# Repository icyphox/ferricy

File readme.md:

# ferricy
> A 34-key split keyboard based on the [Sweep](https://github.com/davidphilipbarr/Sweep/).

Ferricy is a slightly modified version of the Ferris Sweep, sporting a
more industrial look with sharper edges. Notable features:

- Ferricy MX based on the Sweep MX Bling.
- Ferricy Choc based on the Sweep Half-Swept.
- Tenting puck support has been removed (I have no use for it).
- Squared-off edges (plates modified accordingly).
- Larger holes in the PCB for M2 standoffs to pass through.
- The stupid Rust crab is gone.

### MX

| Front | Back |
| :---: | :---: |
|  |  |

### Choc

| Front | Back |
| :---: | :---: |
|  |  |

## license & credits

Ferricy retains [Sweep's
license](https://github.com/davidphilipbarr/Sweep/blob/main/LICENSE).
Thanks to David Barr and all of Sweep's contributors.

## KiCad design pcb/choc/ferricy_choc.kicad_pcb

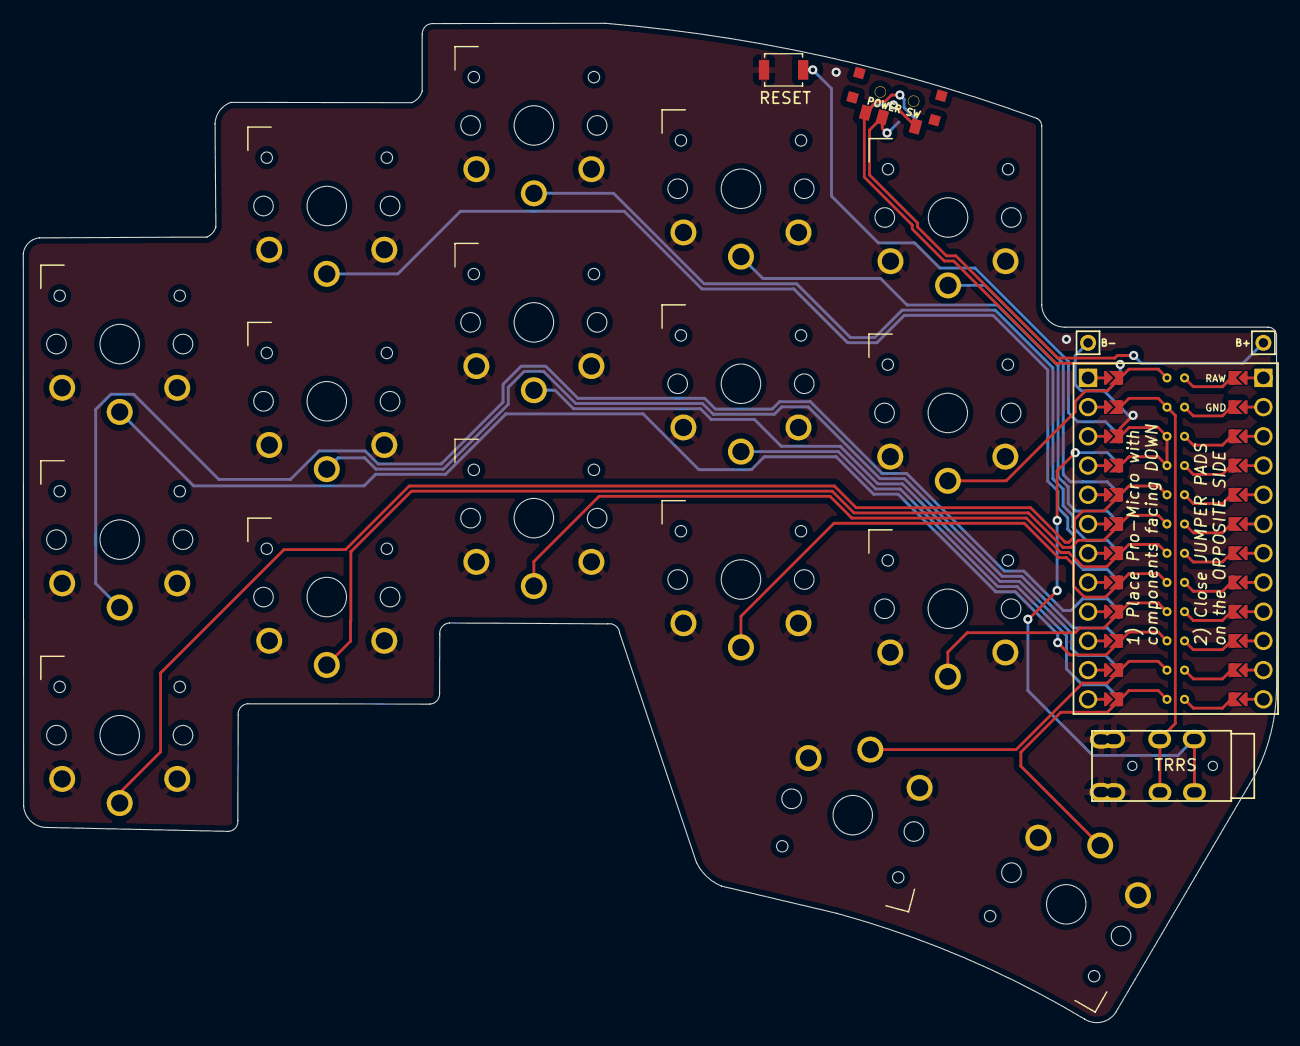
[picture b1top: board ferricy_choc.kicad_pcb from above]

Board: 2 copper layers, 108.9 x 86.9 mm, 23 parts (0 on the bottom side), 23 nets.

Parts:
B+: MountingHole_Pad; 1pin_conn
B-: MountingHole_Pad; 1pin_conn
J2: AudioJack4dpb; TRRS-PJ-DPB2
POWER SW: SW_SPDT; SPDT_C128955
RSW2: SW_Push; Tactile-Switch_SMT
SW1, SW2, SW3, SW4, SW5, SW6, SW7, SW8, SW9, SW10, SW11, SW12, SW13, SW14, SW15, SW16, SW17: SW_Push; SW_PG1350_rev_DPB
U1: ProMicro-kbd; ProMicro_jumpers_facedown

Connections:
BT+_r: B+.1, POWER SW.2
Switch1: SW1.1, U1.10
Switch2: SW2.1, U1.17
Switch3: SW3.1, U1.18
Switch4: SW4.1, U1.19
Switch5: SW5.1, U1.20
Switch6: SW6.1, U1.16
Switch7: SW7.1, U1.15
Switch8: SW8.1, U1.14
Switch9: SW9.1, U1.13
Switch10: SW10.1, U1.1
Switch11: SW11.1, U1.5
Switch12: SW12.1, U1.6
Switch13: SW13.1, U1.7
Switch14: SW14.1, U1.8
Switch15: SW15.1, U1.9
Switch16: SW16.1, U1.11
Switch17: SW17.1, U1.12
Switch18: J2.R1, U1.2
gnd: B-.1, J2.S, J2.T, RSW2.1, RSW2.2, SW1.2, SW2.2, SW3.2, SW4.2, SW5.2, SW6.2, SW7.2, SW8.2, SW9.2, SW10.2, SW11.2, SW12.2, SW13.2, SW14.2, SW15.2, SW16.2, SW17.2, U1.3, U1.4, U1.23
raw: POWER SW.3, U1.24
reset: RSW2.1, RSW2.2, U1.22
vcc: J2.R2, U1.21

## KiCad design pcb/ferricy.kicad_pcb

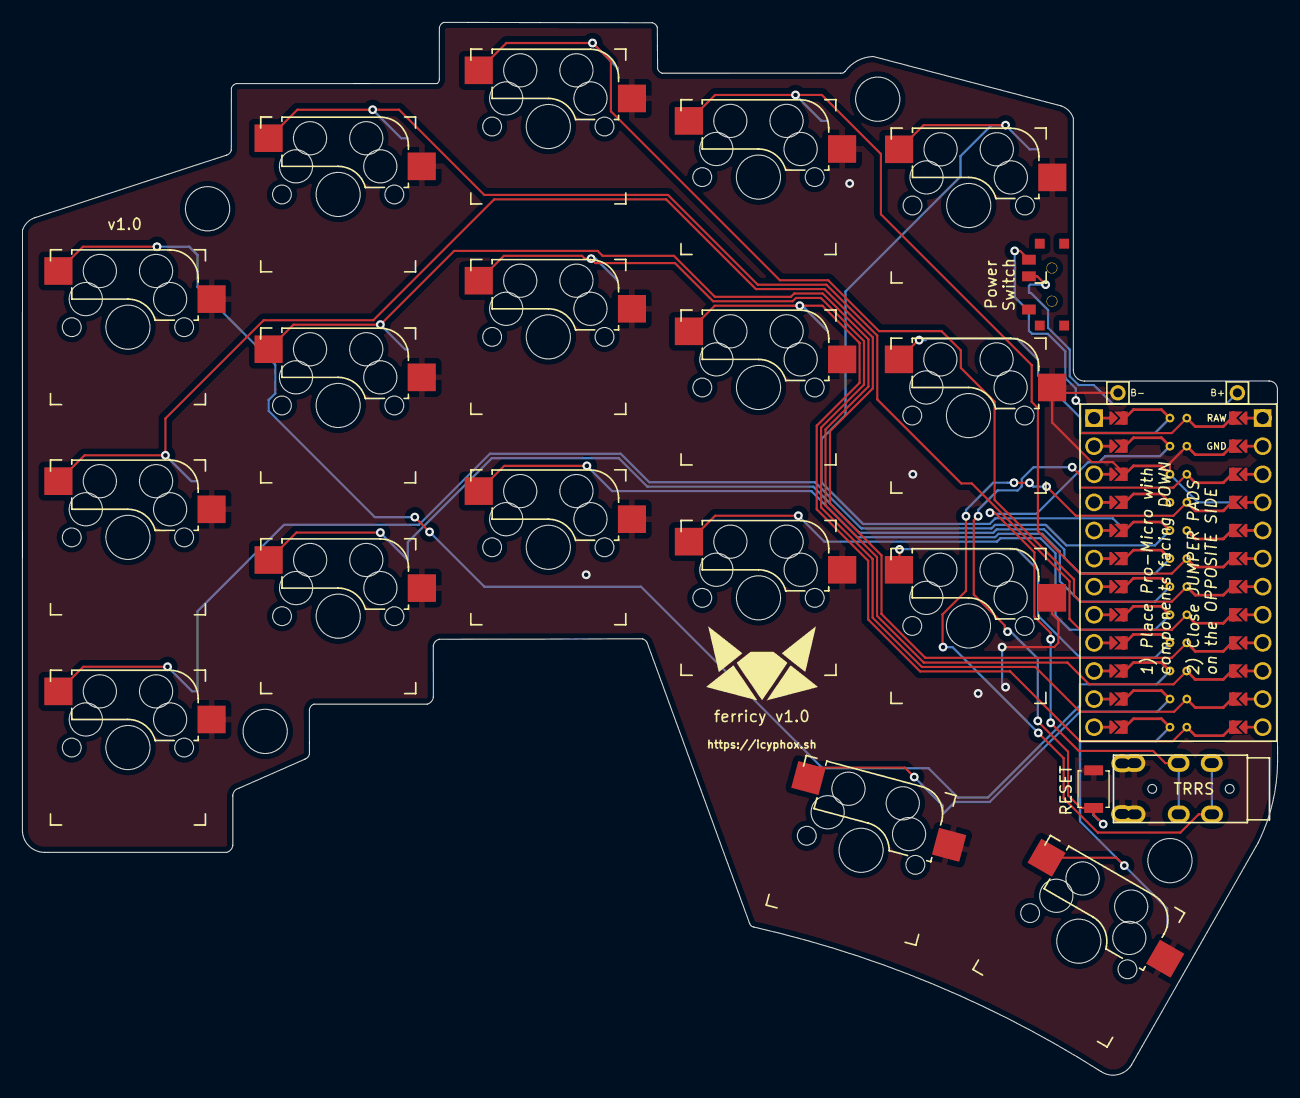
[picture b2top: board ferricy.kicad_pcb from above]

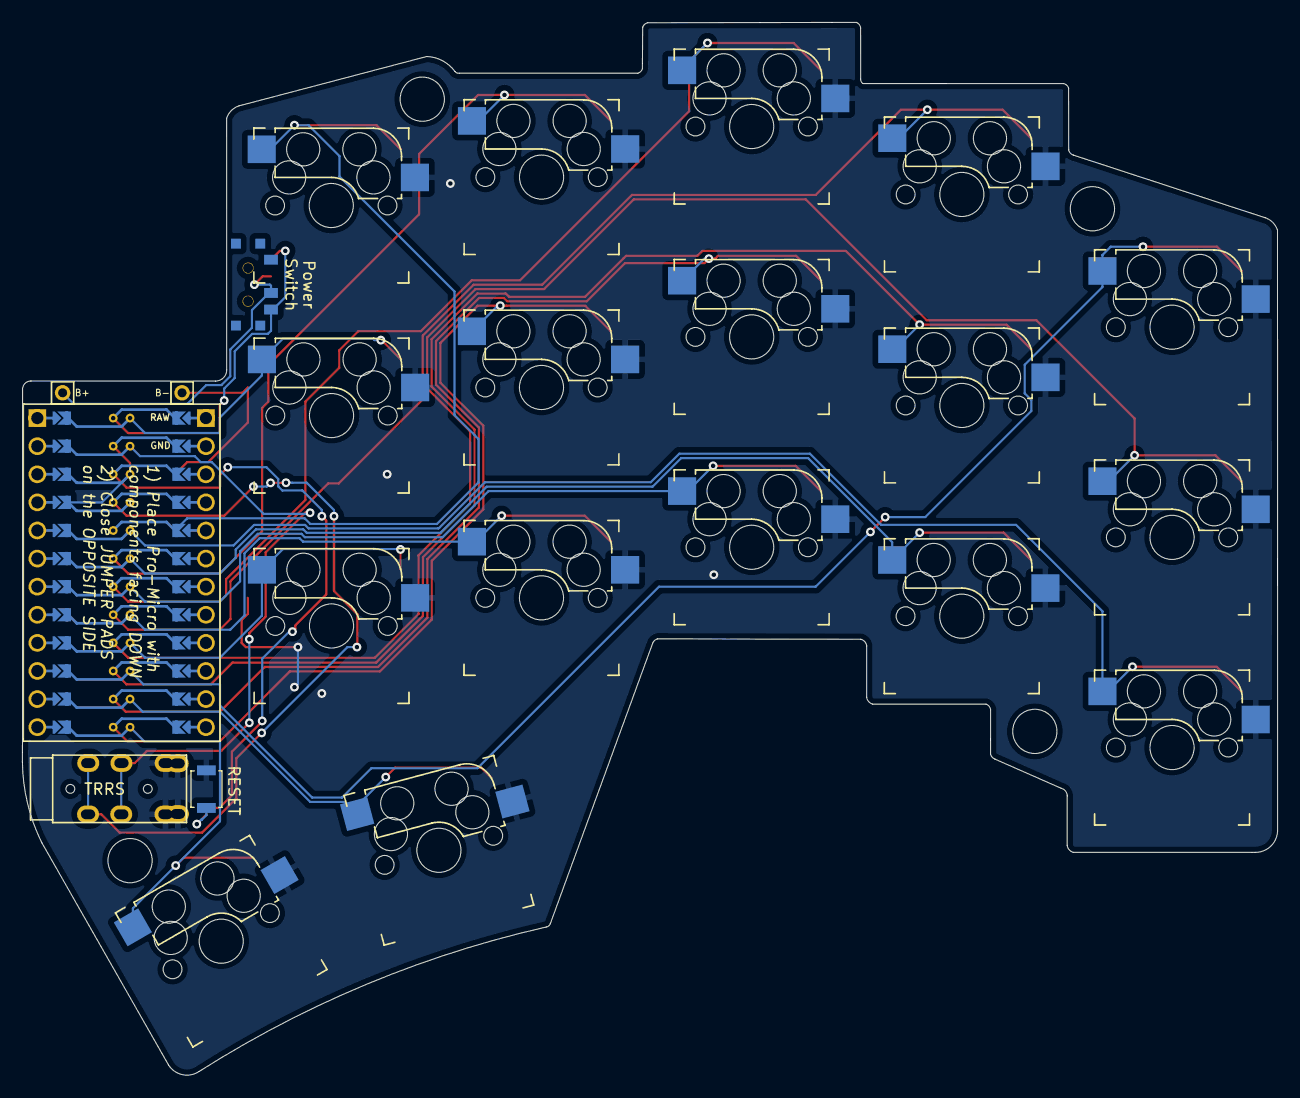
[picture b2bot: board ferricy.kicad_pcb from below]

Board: 2 copper layers, 113.5 x 95.2 mm, 30 parts (2 on the bottom side), 23 nets.

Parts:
.: LOGO; motif
Bat+r1: MountingHole_Pad; 1pin_conn
BatGND1: MountingHole_Pad; 1pin_conn
J2: AudioJack4dpb; TRRS-PJ-DPB2
Mounting 01, Mounting 02, Mounting 03, Mounting 04: MountingHole_3.2mm_M3
RST_B: SW_Push; SW_SPST_B3U-1000P
RST_F: SW_Push; SW_SPST_B3U-1000P
SW2, SW3, SW4, SW5, SW6, SW8, SW9, SW10, SW11, SW12, SW14, SW15, SW16, SW17, SW18, SW20, SW21: SW_Push; Kailh_socket_MX_reversible_sameside
SW_POWERR1: SW_SPDT; SPDT_C128955
SW_POWERR_BK: SW_SPDT; SPDT_C128955r
U1: ProMicro-kbd; ProMicro_facedown

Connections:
BT+_r: Bat+r1.1, SW_POWERR1.2, SW_POWERR_BK.2
Switch1: SW2.1, U1.10
Switch2: SW3.1, U1.17
Switch3: SW4.1, U1.18
Switch4: SW5.1, U1.19
Switch5: SW6.1, U1.20
Switch6: SW8.1, U1.16
Switch7: SW9.1, U1.15
Switch8: SW10.1, U1.14
Switch9: SW11.1, U1.13
Switch10: SW12.1, U1.1
Switch11: SW14.1, U1.5
Switch12: SW15.1, U1.6
Switch13: SW16.1, U1.7
Switch14: SW17.1, U1.8
Switch15: SW18.1, U1.9
Switch16: SW21.1, U1.11
Switch17: SW20.1, U1.12
Switch18: J2.R1, U1.2
gnd: BatGND1.1, J2.S, J2.T, RST_B.1, RST_F.1, SW2.2, SW3.2, SW4.2, SW5.2, SW6.2, SW8.2, SW9.2, SW10.2, SW11.2, SW12.2, SW14.2, SW15.2, SW16.2, SW17.2, SW18.2, SW20.2, SW21.2, U1.3, U1.4, U1.23
raw: SW_POWERR1.3, SW_POWERR_BK.3, U1.24
reset: RST_B.2, RST_F.2, U1.22
vcc: J2.R2, U1.21

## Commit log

2022-07-09 Init
2023-01-06 Add ferricy choc
